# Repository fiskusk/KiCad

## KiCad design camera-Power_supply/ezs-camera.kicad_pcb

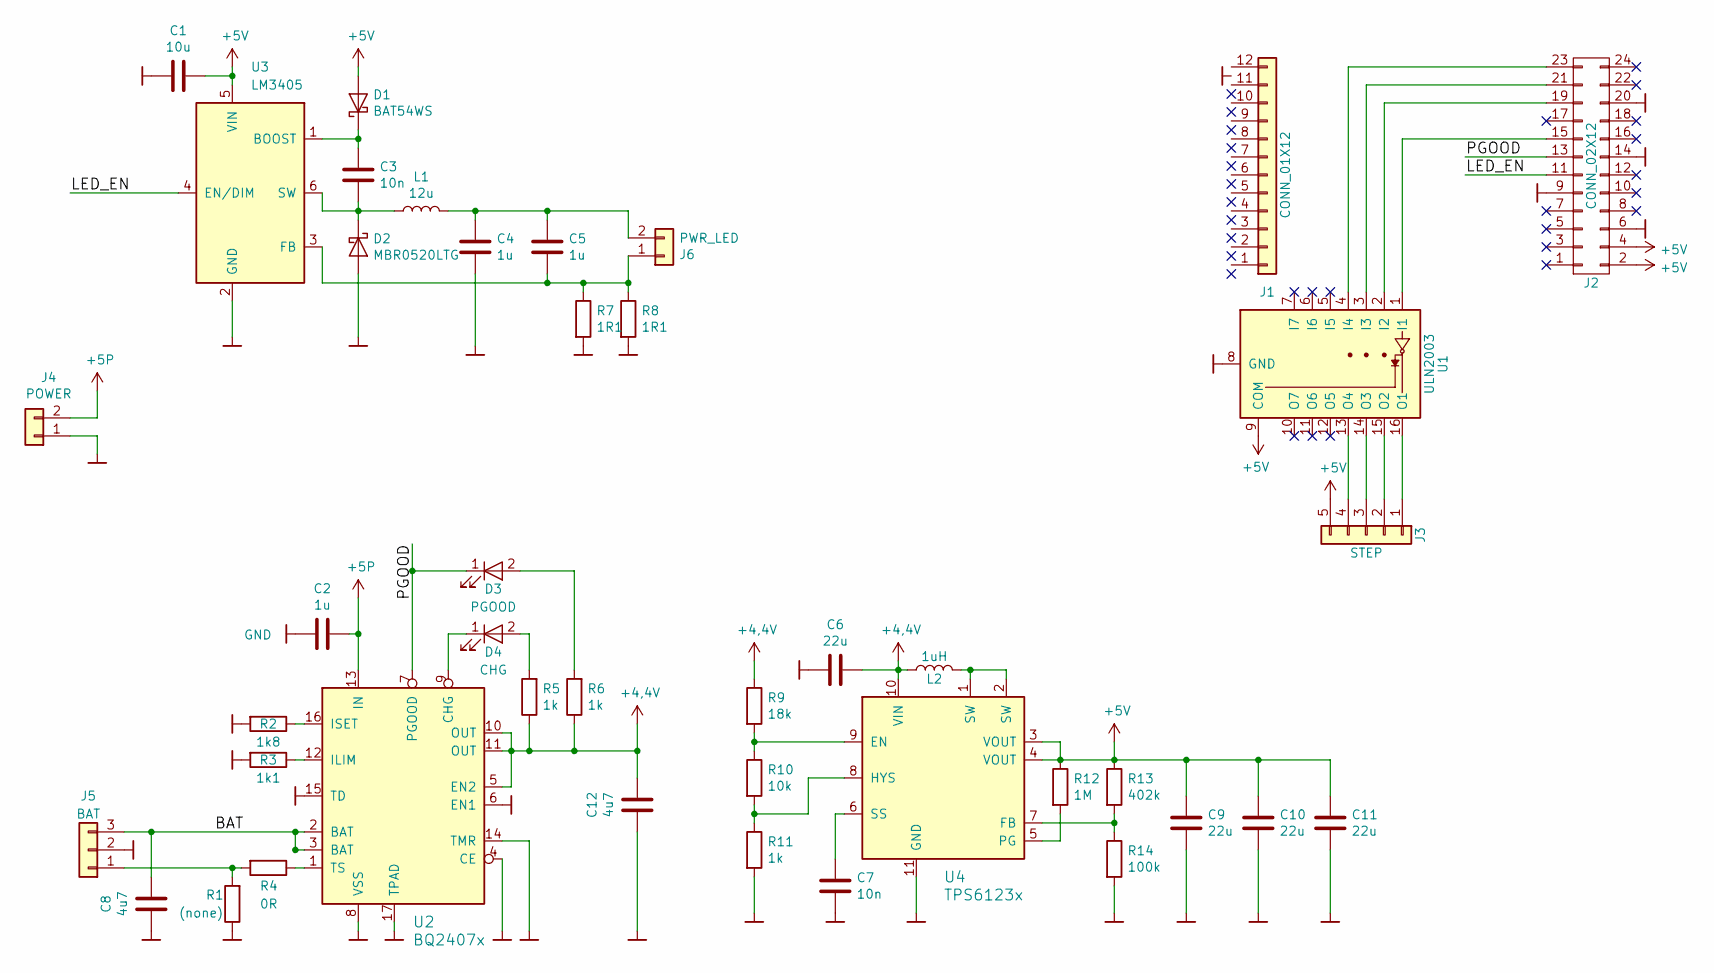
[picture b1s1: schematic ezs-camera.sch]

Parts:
C1: 10u; C_0805_HandSoldering
C2, C4, C5: 1u; C_0805_HandSoldering
C3, C7: 10n; C_0805_HandSoldering
C6, C9, C10, C11: 22u; C_0805_HandSoldering
C8, C12: 4u7; C_0805_HandSoldering
D1: BAT54WS; D_SOD-323_HandSoldering
D2: MBR0520LTG; D_SOD-123
D3: PGOOD; LED_0805_HandSoldering
D4: CHG; LED_0805_HandSoldering
J1: CONN_01X12; Socket_Strip_Straight_1x12_Pitch2.54mm
J2: CONN_02X12; Socket_Strip_Straight_2x12_Pitch2.54mm
J3: STEP; JST_XH_B05B-XH-A_05x2.50mm_Straight
J4: POWER; WireConnection_2.50mmDrill
J5: BAT; JST_XH_B03B-XH-A_03x2.50mm_Straight
J6: PWR_LED; JST_XH_B02B-XH-A_02x2.50mm_Straight
L1: 12u; DLG-0705
L2: 1uH; DJNR3015
R1: (none); R_0805_HandSoldering
R2: 1k8; R_0805_HandSoldering
R3: 1k1; R_0805_HandSoldering
R4: 0R; R_0805_HandSoldering
R5, R6, R11: 1k; R_0805_HandSoldering
R7, R8: 1R1; R_1206_HandSoldering
R9: 18k; R_0805_HandSoldering
R10: 10k; R_0805_HandSoldering
R12: 1M; R_0805_HandSoldering
R13: 402k; R_0805_HandSoldering
R14: 100k; R_0805_HandSoldering
U1: ULN2003; SOIC-16_3.9x9.9mm_Pitch1.27mm
U2: BQ2407x; BQ24073RGTT
U3: LM3405; SOT-23-6
U4: TPS6123x; TPS61232DRCT

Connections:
+4,4V: C6.1, C12.1, L2.1, R5.1, R6.1, R9.1, U2.5 (EN2), U2.10 (OUT), U2.11 (OUT), U4.10 (VIN)
+5P: C2.1, J4.2, U2.13 (IN)
+5V: C1.1, C9.1, C10.1, C11.1, D1.2 (A), J2.2, J2.4, J3.5, R12.1, R13.1, U1.9 (COM), U3.5 (VIN), U4.3 (VOUT), U4.4 (VOUT)
/BAT: C8.1, J5.3, U2.2 (BAT), U2.3 (BAT)
/LED_EN: J2.11, U3.4 (EN/DIM)
/PGOOD: D3.1 (K), J2.13, U2.7 (PGOOD)
GND: C1.2, C2.2, C4.2, C6.2, C7.2, C8.2, C9.2, C10.2, C11.2, C12.2, D2.2 (A), J2.6, J2.9, J2.14, J2.20, J4.1, J5.2, R1.1, R2.2, R3.2, R7.2, R8.2, R11.2, R14.2, U1.8 (GND), U2.4 (CE), U2.6 (EN1), U2.8 (VSS), U2.14 (TMR), U2.15 (TD), U2.17 (TPAD), U3.2 (GND), U4.11 (GND)
unnamed: C3.1, D1.1 (K), U3.1 (BOOST)
unnamed: C3.2, D2.1 (K), L1.1, U3.6 (SW)
unnamed: C4.1, C5.1, J6.2, L1.2
unnamed: C5.2, J6.1, R7.1, R8.1, U3.3 (FB)
unnamed: C7.1, U4.6 (SS)
unnamed: D3.2 (A), R6.2
unnamed: D4.1 (K), U2.9 (CHG)
unnamed: D4.2 (A), R5.2
unnamed: J2.15, U1.1 (I1)
unnamed: J2.19, U1.2 (I2)
unnamed: J2.21, U1.3 (I3)
unnamed: J2.23, U1.4 (I4)
unnamed: J3.1, U1.16 (O1)
unnamed: J3.2, U1.15 (O2)
unnamed: J3.3, U1.14 (O3)
unnamed: J3.4, U1.13 (O4)
unnamed: J5.1, R1.2, R4.2
unnamed: L2.2, U4.1 (SW), U4.2 (SW)
unnamed: R2.1, U2.16 (ISET)
unnamed: R3.1, U2.12 (ILIM)
unnamed: R4.1, U2.1 (TS)
unnamed: R9.2, R10.1, U4.9 (EN)
unnamed: R10.2, R11.1, U4.8 (HYS)
unnamed: R12.2, U4.5 (PG)
unnamed: R13.2, R14.1, U4.7 (FB)

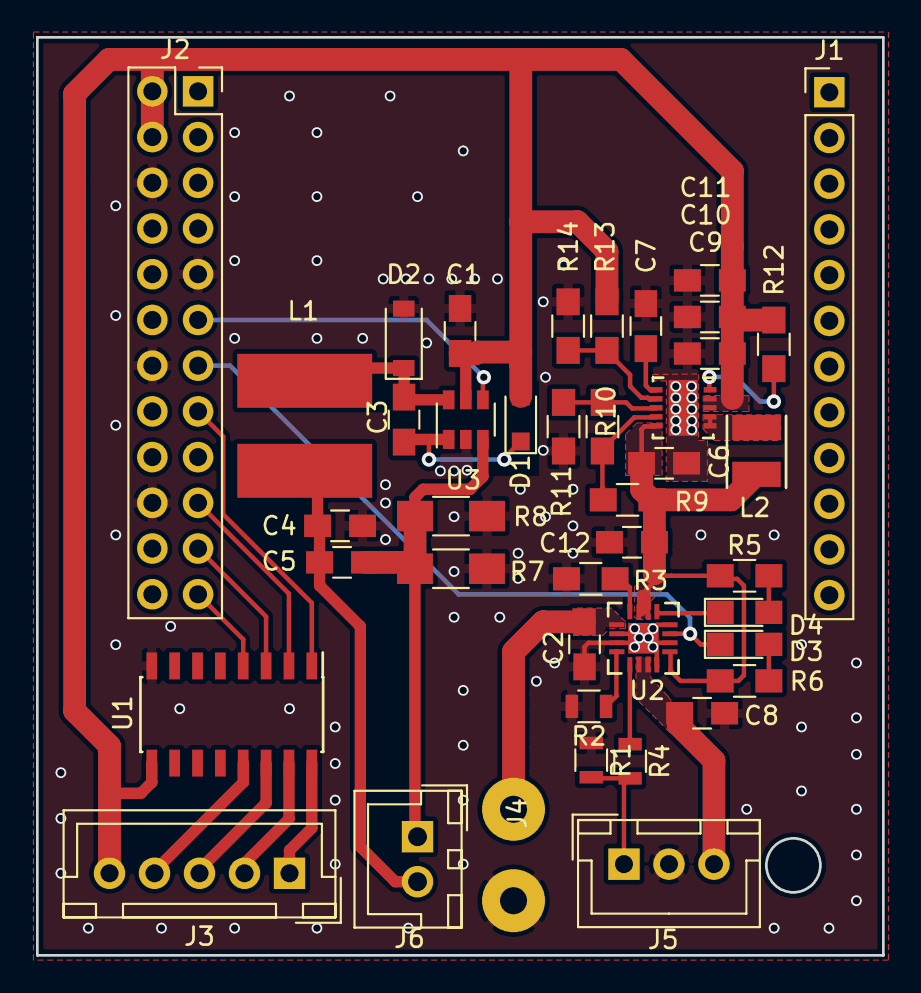
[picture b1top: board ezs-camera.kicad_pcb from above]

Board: 2 copper layers, 47.0 x 51.0 mm, 42 parts (0 on the bottom side), 32 nets.

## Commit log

2017-10-26 first
2017-10-26 v1.0 prvni prototyp odeslany vyrobit
2017-10-26 v1.1 redesign
